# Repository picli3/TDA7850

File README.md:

# TDA7850

Amplificador de audio basado en el **TDA7850**, orientado a una solución multicanal o de alta integración usando un circuito integrado dedicado para audio.

## Propósito del proyecto
Este proyecto busca concentrar en una sola PCB una etapa de amplificación basada en TDA7850, útil para aplicaciones de audio automotriz, doméstico compacto o prototipos multicanal.

## Qué incluye
- esquemático del amplificador
- diseño PCB en KiCad
- base práctica para pruebas y fabricación de una etapa de audio integrada

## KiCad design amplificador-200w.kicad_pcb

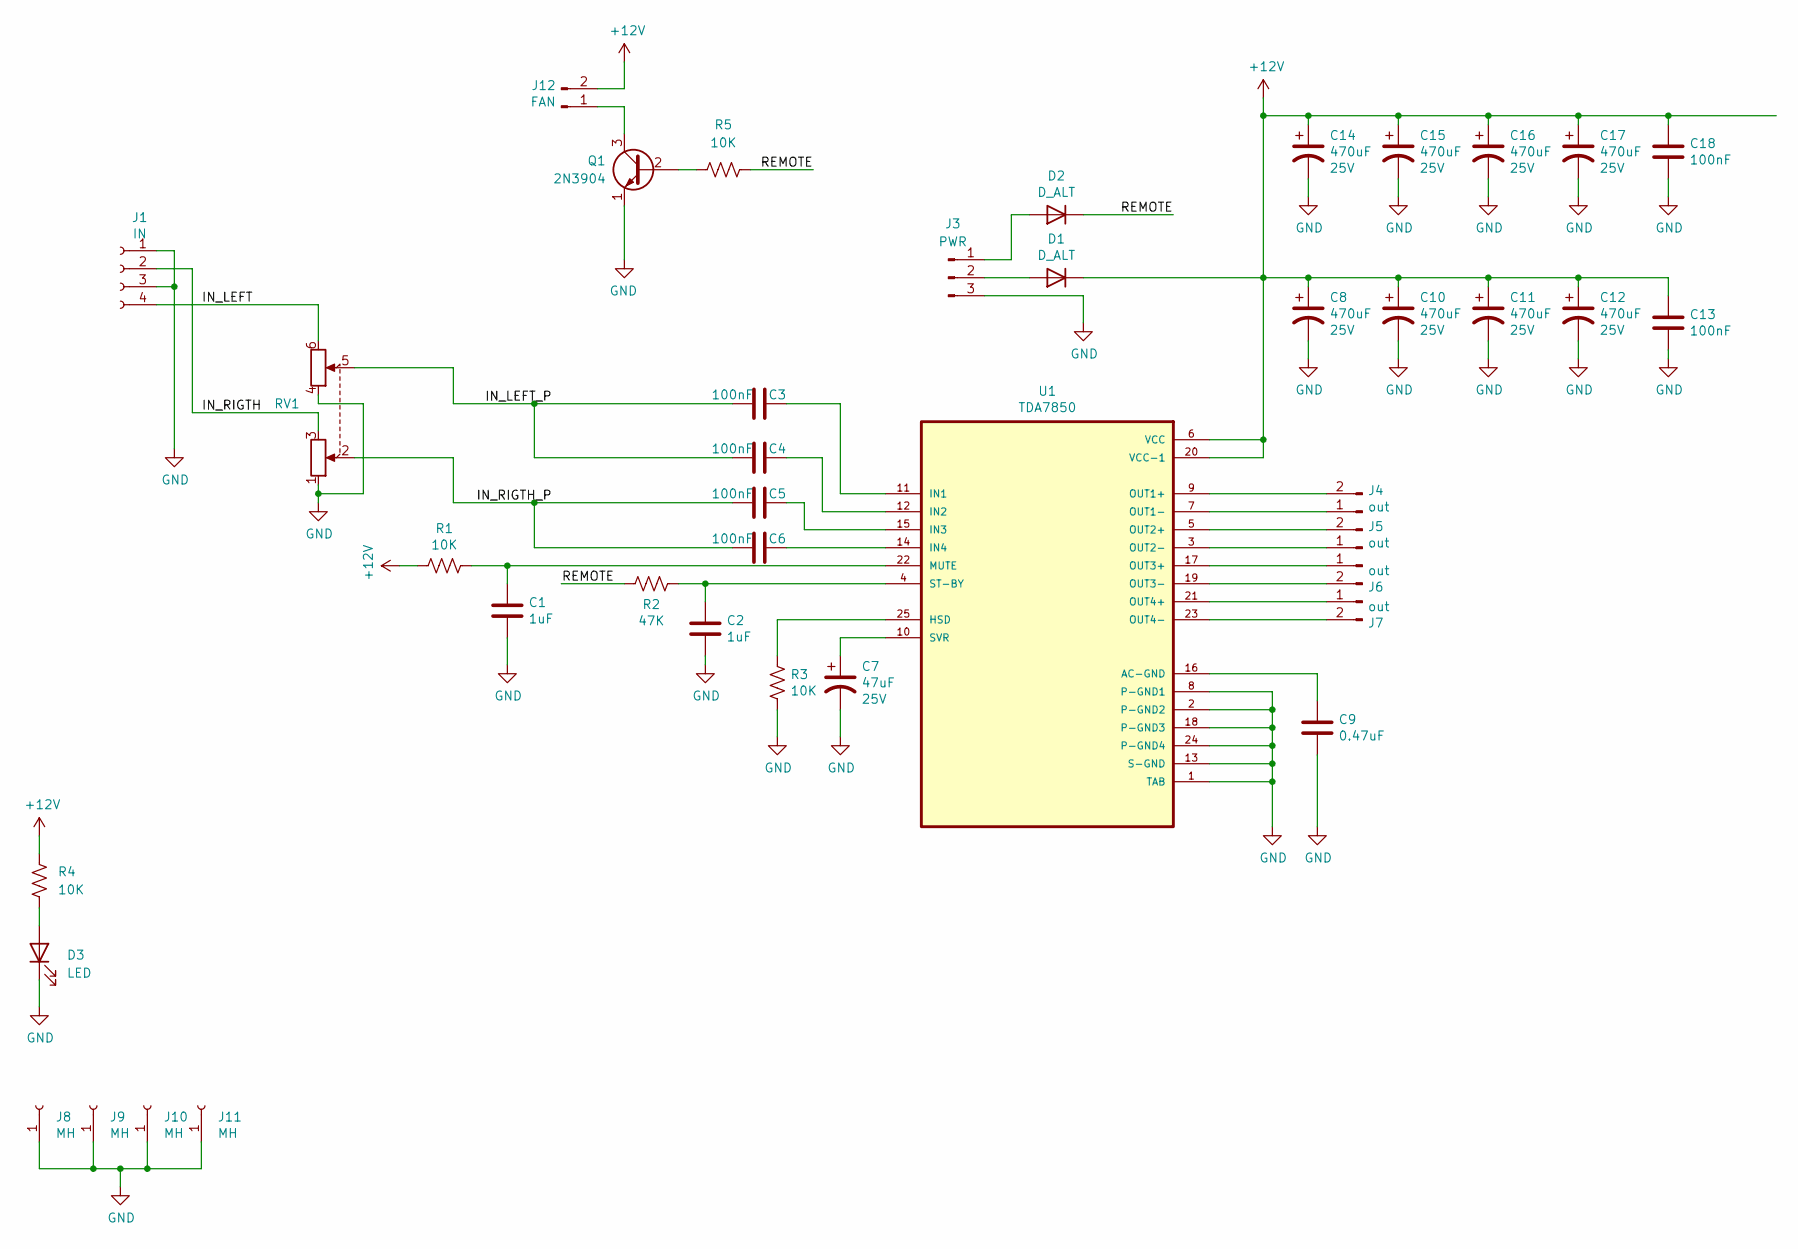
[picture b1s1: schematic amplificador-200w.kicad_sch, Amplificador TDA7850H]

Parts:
C1, C2: 1uF; C_0805_2012Metric
C3, C4, C5, C6, C13, C18: 100nF; C_0603_1608Metric_Pad1.08x0.95mm_HandSolder
C7: 47uF; CP_Radial_D5.0mm_P2.00mm
C8, C10, C11, C12, C14, C15, C16, C17: 470uF; CP_Radial_D10.0mm_P5.00mm
C9: 0.47uF; C_0603_1608Metric_Pad1.08x0.95mm_HandSolder
D1, D2: D_ALT; D_SMA
D3: LED; LED_D3.0mm
J1: IN; CUI_RCJ-21XX; Mfg Part # RCJ-2121
J3: PWR; TE_2-1437667-5; Mfg Part # OSTYK42103030
J4, J5, J6, J7: out; TerminalBlock_Phoenix_MKDS-3-2-5.08_1x02_P5.08mm_Horizontal
J8, J9, J10, J11: MH; MountingHole_3.2mm_M3_Pad_Via
J12: FAN; JST_PH_B2B-PH-K_1x02_P2.00mm_Vertical
Q1: 2N3904; TO-92_Inline
R1, R3, R4, R5: 10K; R_0603_1608Metric
R2: 47K; R_0603_1608Metric
RV1: R_Potentiometer_Dual; Potentiometer_Alps_RK097_Dual_Horizontal
U1: TDA7850; TDA7850H

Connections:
+12V: C8.1, C10.1, C11.1, C12.1, C13.1, C14.1, C15.1, C16.1, C17.1, C18.1, D1.1 (K), J12.2, R1.2, R4.1, U1.6 (VCC), U1.20 (VCC-1)
/IN_LEFT: J1.4, RV1.6
/IN_LEFT_P: C3.2, C4.2, RV1.5
/IN_RIGTH: J1.2, RV1.3
/IN_RIGTH_P: C5.2, C6.2, RV1.2
/REMOTE: D2.1 (K), R2.2, R5.2
GND: C1.2, C2.2, C7.2, C8.2, C9.2, C10.2, C11.2, C12.2, C13.2, C14.2, C15.2, C16.2, C17.2, C18.2, D3.1 (K), J1.1, J1.3, J3.3, J8.1, J9.1, J10.1, J11.1, Q1.1 (E), R3.2, RV1.1, RV1.4, U1.1 (TAB), U1.2 (P-GND2), U1.8 (P-GND1), U1.13 (S-GND), U1.18 (P-GND3), U1.24 (P-GND4)
unnamed: D1.2 (A), J3.2
unnamed: D2.2 (A), J3.1
unnamed: D3.2 (A), R4.2
unnamed: J4.1, U1.7 (OUT1-)
unnamed: J4.2, U1.9 (OUT1+)
unnamed: J5.1, U1.3 (OUT2-)
unnamed: J5.2, U1.5 (OUT2+)
unnamed: J6.1, U1.17 (OUT3+)
unnamed: J6.2, U1.19 (OUT3-)
unnamed: J7.1, U1.21 (OUT4+)
unnamed: J7.2, U1.23 (OUT4-)
unnamed: J12.1, Q1.3 (C)
unnamed: Q1.2 (B), R5.1
unnamed: C9.1, U1.16 (AC-GND)
unnamed: R3.1, U1.25 (HSD)
unnamed: C3.1, U1.11 (IN1)
unnamed: C4.1, U1.12 (IN2)
unnamed: C5.1, U1.15 (IN3)
unnamed: C6.1, U1.14 (IN4)
unnamed: C1.1, R1.1, U1.22 (MUTE)
unnamed: C2.1, R2.1, U1.4 (ST-BY)
unnamed: C7.1, U1.10 (SVR)

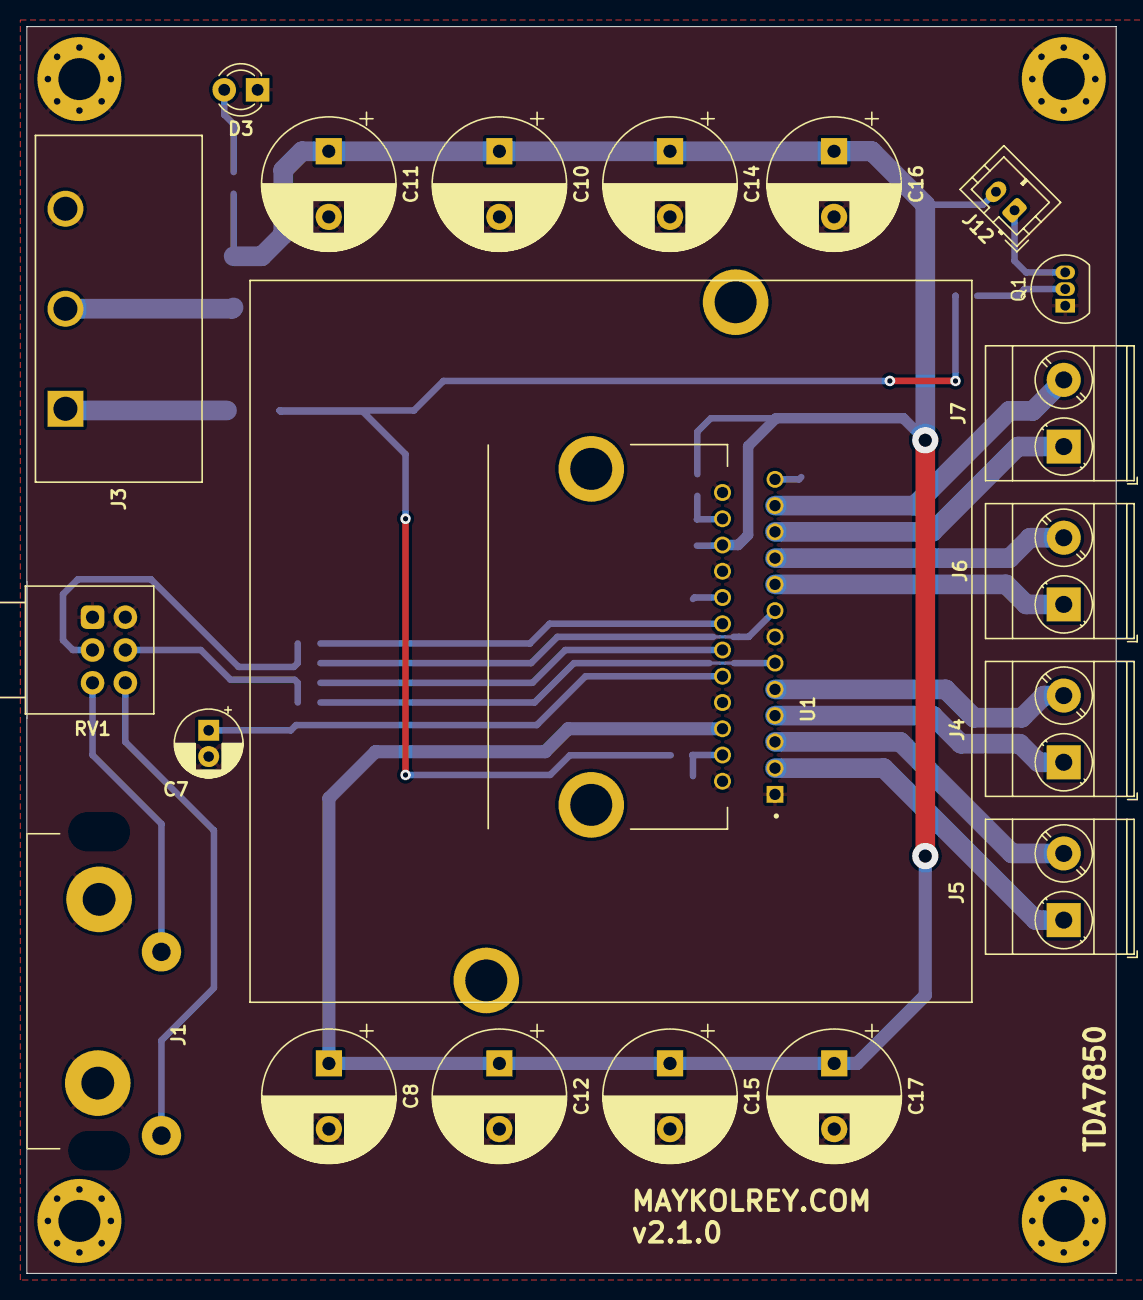
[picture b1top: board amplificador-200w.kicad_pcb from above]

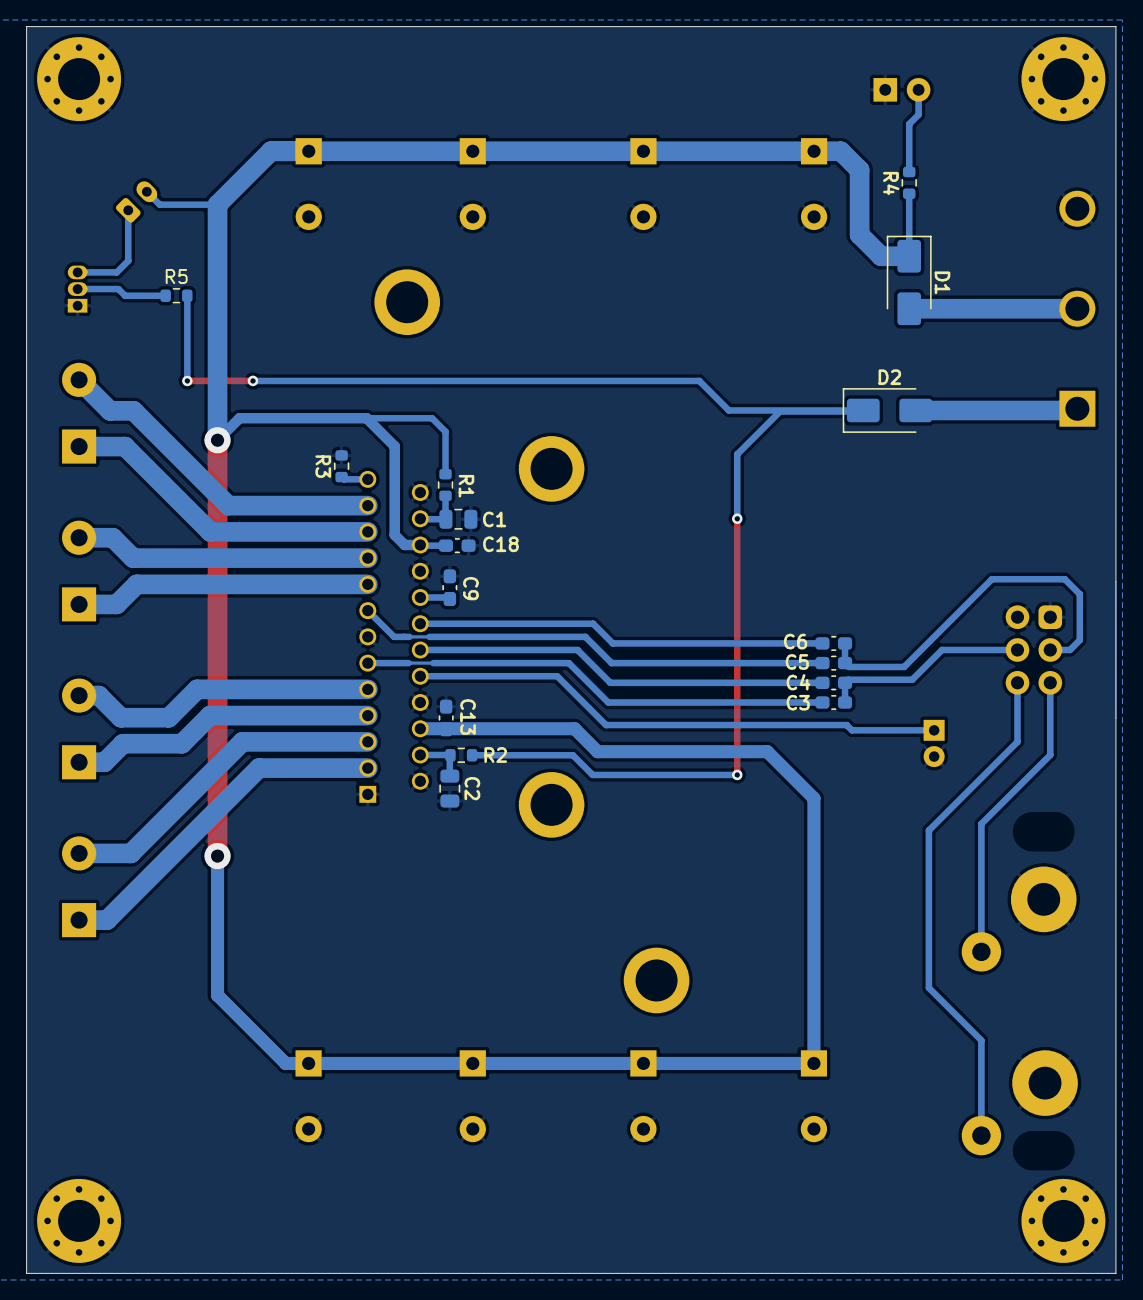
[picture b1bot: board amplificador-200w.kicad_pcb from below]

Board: 2 copper layers, 83.0 x 94.9 mm, 40 parts (16 on the bottom side), 29 nets.

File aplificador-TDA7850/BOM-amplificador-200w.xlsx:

Lista de materiales
Item | Qty | Reference(s) | Value | Mfg Part # | V
1 | 2 | C1, C2 | 1uF
2 | 5 | C3, C4, C5, C6, C13 | 0.1uF
3 | 1 | C7 | 47uF |  | 25V
4 | 8 | C8, C10, C11, C12, C14, C15, C16, C17 | 470uF |  | 25V
5 | 1 | C9 | 0.47uF
6 | 1 | D1 | D_ALT
7 | 1 | J1 | IN | RCJ-2121
8 | 1 | J2 | AUX
9 | 1 | J3 | PWR | OSTYK42103030
10 | 4 | J4, J5, J6, J7 | out
11 | 4 | J8, J9, J10, J11 | MH
12 | 1 | J12 | FAN
13 | 2 | R1, R3 | 10K
14 | 1 | R2 | 47K
15 | 1 | U1 | TDA7850

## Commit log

2020-09-05 listo para producir
2023-07-10 actualizando circuito
2023-07-10 borrando csv
2023-07-10 agregando pdf para metodo planchado
2023-07-29 quitando la entrada de audio auxiliar
2024-07-21 version 2 enviada a fabricar
2024-08-26 corrgiendo disipador y que el ventilador solo prenda con remote
2026-04-29 Agrega README con descripción inicial del proyecto
2026-04-29 Mejora README con descripción específica del proyecto
